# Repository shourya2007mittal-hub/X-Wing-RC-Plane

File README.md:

# X-Wing-RC-Plane

I made a Tailless X-Wing Quad-Motor RC Plane inspired by LEGO with a custom flight controller based on STM32. It is based on STM32 and end design is  inspired by LEGO.

## Features

Microcontroller: STM32F401CBUx<br>
IMU Sensor: MPU-6050 , ICM-20948<br>
Barometer: BMP280<br>
Design inspired by LEGO<br

## Schematic & PCB<br>

 # 3d Render<br>

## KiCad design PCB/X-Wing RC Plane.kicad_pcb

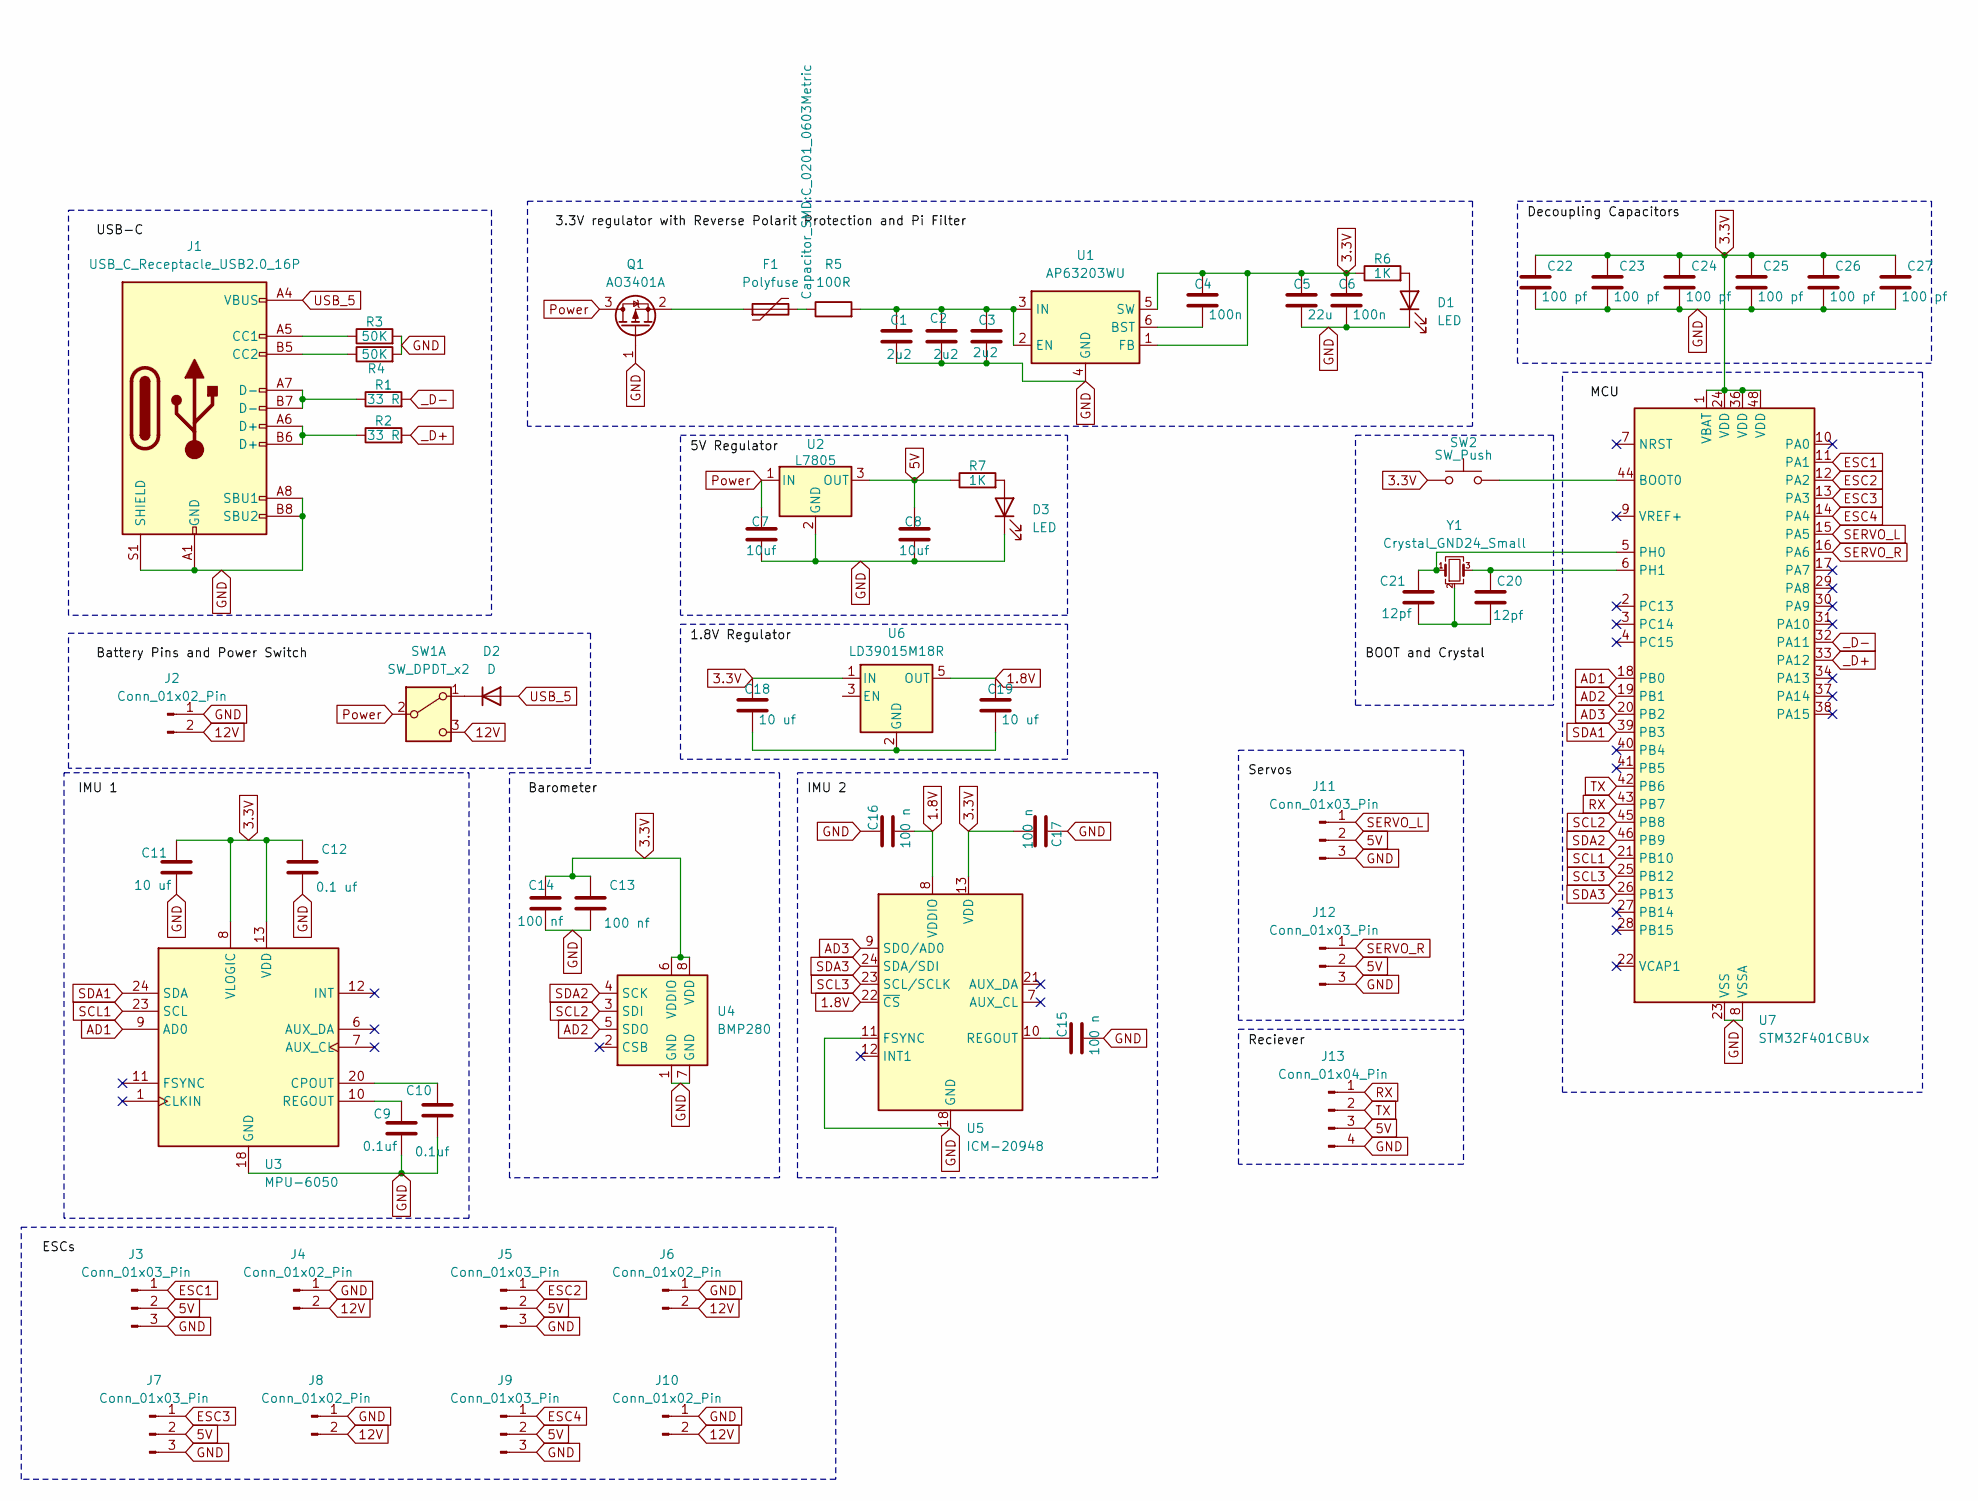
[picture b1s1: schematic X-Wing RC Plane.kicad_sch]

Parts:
C1, C2, C3: 2u2; C_0201_0603Metric
C4, C6: 100n; C_0201_0603Metric
C5: 22u; C_0201_0603Metric
C7, C8: 10uf; C_0201_0603Metric
C9, C10: 0.1uf; C_0201_0603Metric
C11, C18, C19: 10 uf; C_0201_0603Metric
C12: 0.1 uf; C_0201_0603Metric
C13, C14: 100 nf; C_0201_0603Metric
C15, C16, C17: 100 n; C_0201_0603Metric
C20, C21: 12pf; C_0201_0603Metric
C22, C23, C24, C25, C26, C27: 100 pf; C_0201_0603Metric
D1, D3: LED; LED_0201_0603Metric
D2: D; D_0201_0603Metric
F1: Polyfuse; C_0201_0603Metric
J1: USB_C_Receptacle_USB2.0_16P; USB_C_Receptacle_G-Switch_GT-USB-7010ASV
J2: Conn_01x02_Pin; AMASS_XT60-M_1x02_P7.20mm_Vertical
J3, J5, J7, J9, J11, J12: Conn_01x03_Pin; JST_EH_B3B-EH-A_1x03_P2.50mm_Vertical
J4, J6, J8, J10: Conn_01x02_Pin; AMASS_XT60-F_1x02_P7.20mm_Vertical
J13: Conn_01x04_Pin; JST_EH_B4B-EH-A_1x04_P2.50mm_Vertical
Q1: AO3401A; SOT-23
R1, R2: 33 R; R_0201_0603Metric_Pad0.64x0.40mm_HandSolder
R3, R4: 50K; R_0201_0603Metric_Pad0.64x0.40mm_HandSolder
R5: 100R; R_0603_1608Metric
R6, R7: 1K; R_0201_0603Metric_Pad0.64x0.40mm_HandSolder
SW1: SW_DPDT_x2; SW_PUSH_E-Switch_FS5700DP_DPDT
SW2: SW_Push; SW_Tactile_Straight_KSA0Axx1LFTR
U1: AP63203WU; TSOT-23-6
U2: L7805; TO-252-2
U3: MPU-6050; InvenSense_QFN-24_4x4mm_P0.5mm
U4: BMP280; Bosch_LGA-8_2x2.5mm_P0.65mm_ClockwisePinNumbering
U5: ICM-20948; InvenSense_QFN-24_3x3mm_P0.4mm
U6: LD39015M18R; SOT-23-5
U7: STM32F401CBUx; QFN-48-1EP_7x7mm_P0.5mm_EP5.6x5.6mm
Y1: Crystal_GND24_Small; Crystal_SMD_0603-4Pin_6.0x3.5mm

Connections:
1.8V: C16.2, C19.1, U5.8 (VDDIO), U5.22 (~CS), U6.5 (OUT)
3.3V: C4.1, C5.1, C6.1, C11.1, C12.1, C13.1, C14.1, C17.2, C18.1, C22.1, C23.1, C24.1, C25.1, C26.1, C27.1, R6.1, SW2.1, U1.1 (FB), U1.5 (SW), U3.8 (VLOGIC), U3.13 (VDD), U4.6 (VDDIO), U4.8 (VDD), U5.13 (VDD), U6.1 (IN), U7.1 (VBAT), U7.24 (VDD), U7.36 (VDD), U7.48 (VDD)
5V: C8.1, J3.2, J5.2, J7.2, J9.2, J11.2, J12.2, J13.3, R7.1, U2.3 (OUT)
12V: J2.2, J4.2, J6.2, J8.2, J10.2, SW1.3 (C)
AD1: U3.9 (AD0), U7.18 (PB0)
AD2: U4.5 (SDO), U7.19 (PB1)
AD3: U5.9 (SDO/AD0), U7.20 (PB2)
ESC1: J3.1, U7.11 (PA1)
ESC2: J5.1, U7.12 (PA2)
ESC3: J7.1, U7.13 (PA3)
ESC4: J9.1, U7.14 (PA4)
GND: C1.2, C2.2, C3.2, C5.2, C6.2, C7.2, C8.2, C9.2, C10.2, C11.2, C12.2, C13.2, C14.2, C15.2, C16.1, C17.1, C22.2, C23.2, C24.2, C25.2, C26.2, C27.2, D1.1 (K), D3.1 (K), J1.A1 (GND), J1.A8 (SBU1), J1.A12 (GND), J1.B1 (GND), J1.B8 (SBU2), J1.B12 (GND), J1.S1 (SHIELD), J2.1, J3.3, J4.1, J5.3, J6.1, J7.3, J8.1, J9.3, J10.1, J11.3, J12.3, J13.4, Q1.1 (G), R3.2, R4.2, U1.4 (GND), U2.2 (GND), U3.18 (GND), U4.1 (GND), U4.7 (GND), U5.11 (FSYNC), U5.18 (GND), U5.20 (GND), U7.8 (VSSA), U7.23 (VSS), U7.35 (VSS), U7.47 (VSS), U7.49 (VSS)
unnamed: C20.2, C21.2, Y1.2 (G), Y1.4 (G)
unnamed: D1.2 (A), R6.2
unnamed: D2.1 (K), SW1.1 (A)
unnamed: D3.2 (A), R7.2
unnamed: F1.2, R5.1
unnamed: J1.A5 (CC1), R3.1
unnamed: J1.B5 (CC2), R4.1
unnamed: J1.A6 (D+), J1.B6 (D+), R2.1
unnamed: J1.A7 (D-), J1.B7 (D-), R1.1
unnamed: F1.1, Q1.2 (S)
unnamed: C4.2, U1.6 (BST)
unnamed: C1.1, C2.1, C3.1, R5.2, U1.2 (EN), U1.3 (IN)
unnamed: C10.1, U3.20 (CPOUT)
unnamed: C9.1, U3.10 (REGOUT)
unnamed: C15.1, U5.10 (REGOUT)
unnamed: C18.2, C19.2, U6.2 (GND)
unnamed: SW2.2, U7.44 (BOOT0)
unnamed: C21.1, U7.5 (PH0), Y1.1
unnamed: C20.1, U7.6 (PH1), Y1.3
Power: C7.1, Q1.3 (D), SW1.2 (B), U2.1 (IN)
RX: J13.1, U7.43 (PB7)
SCL1: U3.23 (SCL), U7.21 (PB10)
SCL2: U4.3 (SDI), U7.45 (PB8)
SCL3: U5.23 (SCL/SCLK), U7.25 (PB12)
SDA1: U3.24 (SDA), U7.39 (PB3)
SDA2: U4.4 (SCK), U7.46 (PB9)
SDA3: U5.24 (SDA/SDI), U7.26 (PB13)
SERVO_L: J11.1, U7.15 (PA5)
SERVO_R: J12.1, U7.16 (PA6)
TX: J13.2, U7.42 (PB6)
USB_5: D2.2 (A), J1.A4 (VBUS), J1.A9 (VBUS), J1.B4 (VBUS), J1.B9 (VBUS)
_D+: R2.2, U7.33 (PA12)
_D-: R1.2, U7.32 (PA11)

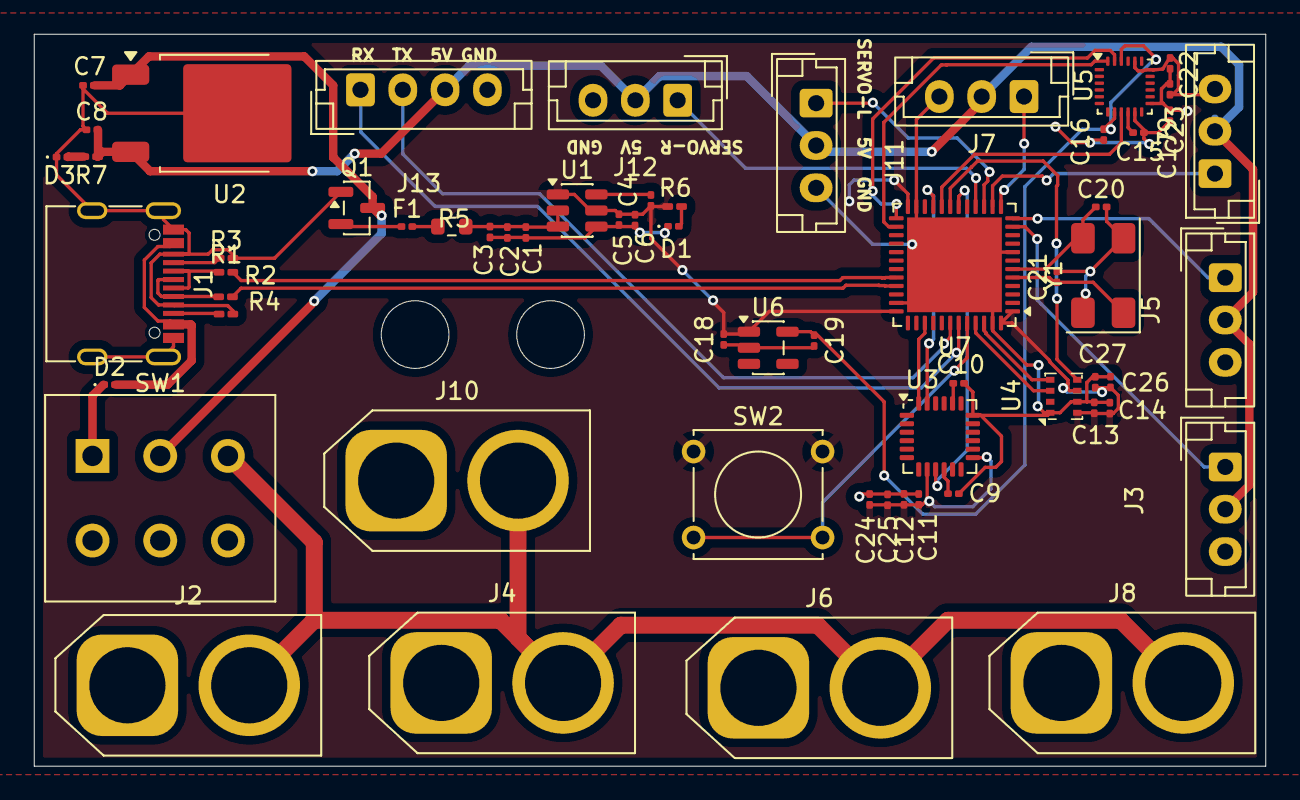
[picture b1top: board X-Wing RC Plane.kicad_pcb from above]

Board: 2 copper layers, 72.8 x 43.2 mm, 62 parts (0 on the bottom side), 45 nets.
